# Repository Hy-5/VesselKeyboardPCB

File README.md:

# VesselKeyboardPCB
 Building a 75%(ish) custom ISO keyboard PCB

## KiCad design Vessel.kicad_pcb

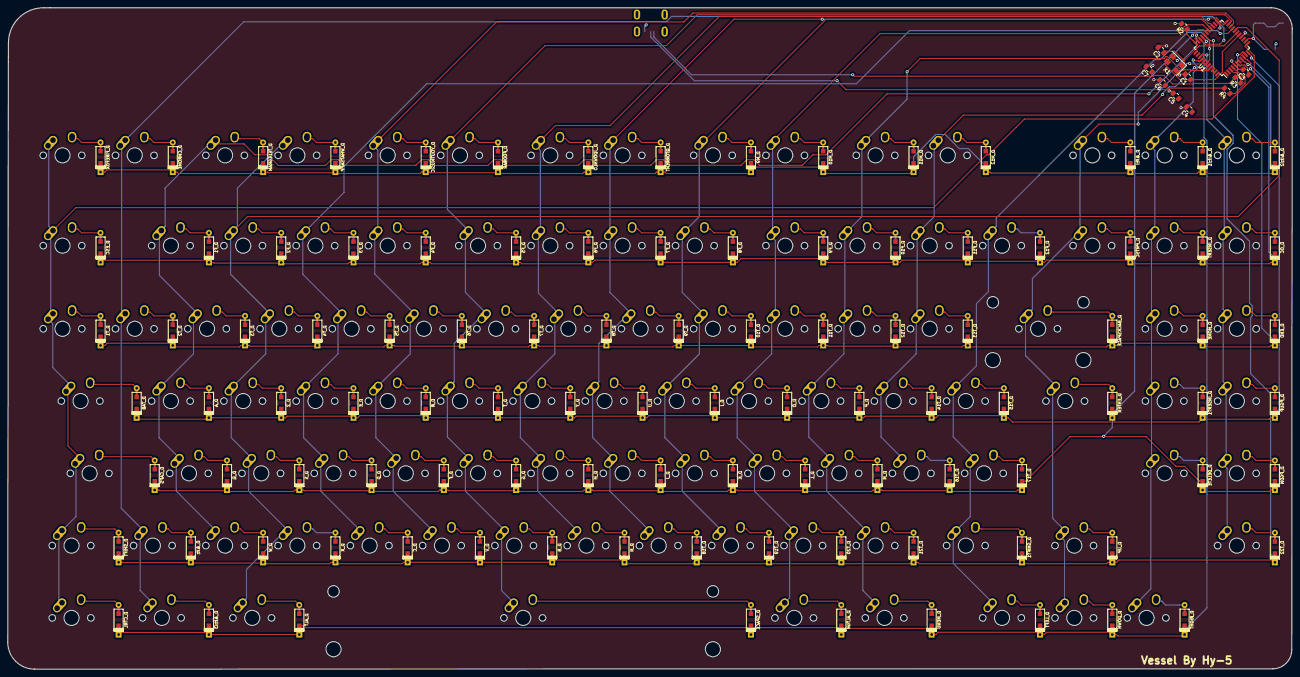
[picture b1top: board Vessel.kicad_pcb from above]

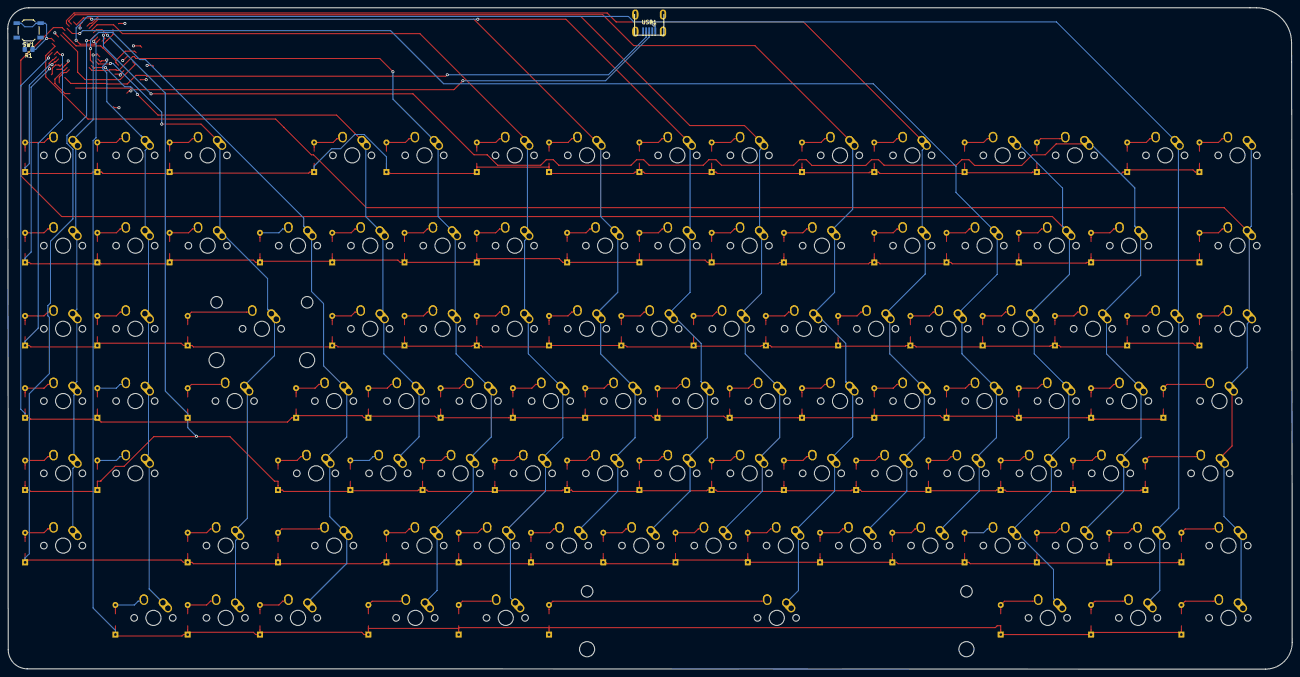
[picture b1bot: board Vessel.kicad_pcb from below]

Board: 2 copper layers, 338.6 x 174.3 mm, 219 parts (3 on the bottom side), 137 nets.

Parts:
C1, C2, C3, C4, C5, C6, C7: 22pF; C_0805_2012Metric_Pad1.15x1.40mm_HandSolder
D_&lt;: D; D_SOD123_axial
D_&lt;I, D_&lt;I1, D_&lt;I2, D_&lt;I3: D; D_SOD123_axial
D_A: D; D_SOD123_axial
D_ALT: D; D_SOD123_axial
D_ALTGR: D; D_SOD123_axial
D_B: D; D_SOD123_axial
D_BACKSPACE: D; D_SOD123_axial
D_C: D; D_SOD123_axial
D_CAPS: D; D_SOD123_axial
D_CHROME: D; D_SOD123_axial
D_CTRL: D; D_SOD123_axial
D_D: D; D_SOD123_axial
D_DELETE: D; D_SOD123_axial
D_DOWN: D; D_SOD123_axial
D_E: D; D_SOD123_axial
D_END: D; D_SOD123_axial
D_ENTER: D; D_SOD123_axial
D_ESC: D; D_SOD123_axial
D_F, D_F1, D_F2, D_F3, D_F4, D_F5, D_F6, D_F7, D_F8, D_F9, D_F10, D_F11, D_F12: D; D_SOD123_axial
D_FIREFOX: D; D_SOD123_axial
D_FOOBAR: D; D_SOD123_axial
D_G: D; D_SOD123_axial
D_H: D; D_SOD123_axial
D_HOME: D; D_SOD123_axial
D_I: D; D_SOD123_axial
D_INSERT, D_INSERT1: D; D_SOD123_axial
D_J: D; D_SOD123_axial
D_JDOWNLO: D; D_SOD123_axial
D_K: D; D_SOD123_axial
D_L: D; D_SOD123_axial
D_LEFT: D; D_SOD123_axial
D_M, D_M9, D_M10, D_M11, D_M12: D; D_SOD123_axial
D_MENU: D; D_SOD123_axial
D_N: D; D_SOD123_axial
D_O: D; D_SOD123_axial
D_OC: D; D_SOD123_axial
D_P: D; D_SOD123_axial
D_PGDN: D; D_SOD123_axial
D_PGUP: D; D_SOD123_axial
D_PRTSC: D; D_SOD123_axial
D_Q: D; D_SOD123_axial
D_QTORRENT: D; D_SOD123_axial
D_R: D; D_SOD123_axial
D_RIGHT: D; D_SOD123_axial
D_S: D; D_SOD123_axial
D_SHIFT, D_SHIFT1: D; D_SOD123_axial
D_SPACE: D; D_SOD123_axial
D_T, D_T1, D_T2, D_T3, D_T4, D_T5, D_T6, D_T7, D_T8, D_T9, D_T10, D_T11, D_T12, D_T13, D_T14, D_T15, D_T16, D_T17, D_T18, D_T19, D_T20, D_T21, D_T22: D; D_SOD123_axial
D_TAB: D; D_SOD123_axial
D_TELEGRAM: D; D_SOD123_axial
D_U: D; D_SOD123_axial
D_UP: D; D_SOD123_axial
D_V: D; D_SOD123_axial
D_W: D; D_SOD123_axial
D_WHATSAPP: D; D_SOD123_axial
D_X: D; D_SOD123_axial
D_Y: D; D_SOD123_axial
D_YOUTMUSIC: D; D_SOD123_axial
D_Z: D; D_SOD123_axial
K_&lt;: KEYSW; MX-1U-NoLED
K_&lt;I, K_&lt;I1, K_&lt;I2: KEYSW; MX-1U-NoLED
K_&lt;I3: KEYSW; MX-1.25U-NoLED
K_A: KEYSW; MX-1U-NoLED
K_ALT: KEYSW; MX-1.25U-NoLED
K_ALTGR: KEYSW; MX-1.25U-NoLED
K_B: KEYSW; MX-1U-NoLED
K_BACKSPACE: KEYSW; MX-2U-NoLED
K_C: KEYSW; MX-1U-NoLED
K_CAPS: KEYSW; MX-1.75U-NoLED
K_CHROME: KEYSW; MX-1U-NoLED
K_CTRL: KEYSW; MX-1.25U-NoLED
K_D: KEYSW; MX-1U-NoLED
K_DELETE: KEYSW; MX-1U-NoLED
K_DOWN: KEYSW; MX-1U-NoLED
K_E: KEYSW; MX-1U-NoLED
K_END: KEYSW; MX-1U-NoLED
K_ENTER: KEYSW; MX-1.25U-NoLED
K_ESC: KEYSW; MX-1U-NoLED
K_F, K_F1, K_F2, K_F3, K_F4, K_F5, K_F6, K_F7, K_F8, K_F9, K_F10, K_F11, K_F12: KEYSW; MX-1U-NoLED
K_FIREFOX: KEYSW; MX-1U-NoLED
K_FOOBAR: KEYSW; MX-1U-NoLED
K_G: KEYSW; MX-1U-NoLED
K_H: KEYSW; MX-1U-NoLED
K_HOME: KEYSW; MX-1U-NoLED
K_I: KEYSW; MX-1U-NoLED
K_INSERT, K_INSERT1: KEYSW; MX-1U-NoLED
K_J: KEYSW; MX-1U-NoLED
K_JDOWNLO: KEYSW; MX-1U-NoLED
K_K: KEYSW; MX-1U-NoLED
K_L: KEYSW; MX-1U-NoLED
K_LEFT: KEYSW; MX-1U-NoLED
K_M, K_M9, K_M10, K_M11, K_M12: KEYSW; MX-1U-NoLED
K_MENU: KEYSW; MX-1.25U-NoLED
K_N: KEYSW; MX-1U-NoLED
K_O: KEYSW; MX-1U-NoLED
K_OC: KEYSW; MX-1U-NoLED
K_P: KEYSW; MX-1U-NoLED
K_PGDN: KEYSW; MX-1U-NoLED
K_PGUP: KEYSW; MX-1U-NoLED
K_PRTSC: KEYSW; MX-1U-NoLED
K_Q: KEYSW; MX-1U-NoLED
K_QTORRENT: KEYSW; MX-1U-NoLED
K_R: KEYSW; MX-1U-NoLED
K_RIGHT: KEYSW; MX-1U-NoLED
K_S: KEYSW; MX-1U-NoLED
K_SHIFT: KEYSW; MX-1.25U-NoLED
K_SHIFT1: KEYSW; MX-1.5U-NoLED
K_SPACE: KEYSW; MX-6.25U-NoLED
K_T, K_T1, K_T2, K_T3, K_T4, K_T5, K_T6, K_T7, K_T8, K_T9, K_T10, K_T11, K_T12, K_T13, K_T14, K_T15, K_T16, K_T17, K_T18, K_T19, K_T20, K_T21, K_T22: KEYSW; MX-1U-NoLED
K_TAB: KEYSW; MX-1.5U-NoLED
K_TELEGRAM: KEYSW; MX-1U-NoLED
K_U: KEYSW; MX-1U-NoLED
K_UP: KEYSW; MX-1U-NoLED
K_V: KEYSW; MX-1U-NoLED
K_W: KEYSW; MX-1U-NoLED
K_WHATSAPP: KEYSW; MX-1U-NoLED
K_X: KEYSW; MX-1U-NoLED
K_Y: KEYSW; MX-1U-NoLED
K_YOUTMUSIC: KEYSW; MX-1U-NoLED
K_Z: KEYSW; MX-1U-NoLED
R1, R2: 10k; R_0805_2012Metric_Pad1.15x1.40mm_HandSolder
R3, R4: 22; R_0805_2012Metric_Pad1.15x1.40mm_HandSolder
SW1: SW_PUSH; SW_SPST_TL3342
U1: ATMEGA32U4; TQFP-44_10x10mm_P0.8mm
USB1: Molex-0548190589; Molex-0548190589-Assembly
X1: XTAL_GND; Crystal_SMD_5032-4Pin_5.0x3.2mm

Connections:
/col0: K_CAPS.1, K_CTRL.1, K_ESC.1, K_FIREFOX.1, K_SHIFT.1, K_T1.1, K_TAB.1, U1.12
/col1: K_&lt;.1, K_&lt;I3.1, K_CHROME.1, K_T2.1, U1.31
/col2: K_A.1, K_F1.1, K_Q.1, K_T3.1, K_TELEGRAM.1, K_W.1, U1.32
/col3: K_ALT.1, K_F2.1, K_S.1, K_T4.1, K_WHATSAPP.1, K_X.1, K_Z.1, U1.18
/col4: K_C.1, K_D.1, K_E.1, K_F3.1, K_T5.1, U1.19
/col5: K_F.1, K_F4.1, K_R.1, K_T6.1, K_V.1, K_YOUTMUSIC.1, U1.20
/col6: K_B.1, K_F5.1, K_FOOBAR.1, K_G.1, K_SPACE.1, K_T.1, K_T7.1, U1.21
/col7: K_F6.1, K_H.1, K_JDOWNLO.1, K_N.1, K_T8.1, K_Y.1, U1.25
/col8: K_F7.1, K_J.1, K_QTORRENT.1, K_T9.1, K_T18.1, K_U.1, U1.22
/col9: K_F8.1, K_I.1, K_K.1, K_M9.1, K_T10.1, K_T19.1, U1.26
/col10: K_ALTGR.1, K_F9.1, K_L.1, K_M10.1, K_O.1, K_T11.1, K_T20.1, U1.27
/col11: K_F10.1, K_M.1, K_M11.1, K_MENU.1, K_P.1, K_T12.1, K_T21.1, U1.41
/col12: K_F11.1, K_M12.1, K_T13.1, K_T14.1, K_T16.1, U1.40
/col13: K_F12.1, K_LEFT.1, K_SHIFT1.1, K_T15.1, K_T17.1, U1.39
/col14: K_&lt;I.1, K_BACKSPACE.1, K_DOWN.1, K_ENTER.1, K_PRTSC.1, K_UP.1, U1.38
/col15: K_&lt;I1.1, K_DELETE.1, K_HOME.1, K_INSERT.1, K_INSERT1.1, K_RIGHT.1, U1.37
/col16: K_&lt;I2.1, K_END.1, K_OC.1, K_PGDN.1, K_PGUP.1, K_T22.1, U1.36
/row0: D_&lt;I.1, D_&lt;I1.1, D_&lt;I2.1, D_CHROME.1, D_FIREFOX.1, D_FOOBAR.1, D_JDOWNLO.1, D_M9.1, D_M10.1, D_M11.1, D_M12.1, D_QTORRENT.1, D_TELEGRAM.1, D_WHATSAPP.1, D_YOUTMUSIC.1, U1.8
/row1: D_ESC.1, D_F1.1, D_F2.1, D_F3.1, D_F4.1, D_F5.1, D_F6.1, D_F7.1, D_F8.1, D_F9.1, D_F10.1, D_F11.1, D_F12.1, D_INSERT.1, D_OC.1, D_PRTSC.1, U1.9
/row2: D_BACKSPACE.1, D_END.1, D_HOME.1, D_T1.1, D_T2.1, D_T3.1, D_T4.1, D_T5.1, D_T6.1, D_T7.1, D_T8.1, D_T9.1, D_T10.1, D_T11.1, D_T12.1, D_T13.1, U1.10
/row3: D_A.1, D_E.1, D_I.1, D_INSERT1.1, D_O.1, D_P.1, D_PGUP.1, D_R.1, D_T.1, D_T14.1, D_T15.1, D_TAB.1, D_U.1, D_Y.1, D_Z.1, U1.11
/row4: D_CAPS.1, D_D.1, D_DELETE.1, D_ENTER.1, D_F.1, D_G.1, D_H.1, D_J.1, D_K.1, D_L.1, D_M.1, D_PGDN.1, D_Q.1, D_S.1, D_T16.1, D_T17.1, U1.28
/row5: D_&lt;.1, D_B.1, D_C.1, D_N.1, D_SHIFT.1, D_SHIFT1.1, D_T18.1, D_T19.1, D_T20.1, D_T21.1, D_T22.1, D_UP.1, D_V.1, D_W.1, D_X.1, U1.29
/row6: D_&lt;I3.1, D_ALT.1, D_ALTGR.1, D_CTRL.1, D_DOWN.1, D_LEFT.1, D_MENU.1, D_RIGHT.1, D_SPACE.1, U1.30
GND: C1.2, C2.2, C3.2, C4.2, C5.2, C6.2, C7.2, R2.2, SW1.1, U1.5, U1.15, U1.23, USB1.1, X1.2, X1.4
unnamed: C1.1, U1.16, X1.1
unnamed: C2.1, U1.17, X1.3
unnamed: C3.1, U1.6
unnamed: D_&lt;.2, K_&lt;.2
unnamed: D_&lt;I1.2, K_&lt;I1.2
unnamed: D_&lt;I2.2, K_&lt;I2.2
unnamed: D_&lt;I3.2, K_&lt;I3.2
unnamed: D_&lt;I.2, K_&lt;I.2
unnamed: D_A.2, K_A.2
unnamed: D_ALT.2, K_ALT.2
unnamed: D_ALTGR.2, K_ALTGR.2
unnamed: D_B.2, K_B.2
unnamed: D_BACKSPACE.2, K_BACKSPACE.2
unnamed: D_C.2, K_C.2
unnamed: D_CAPS.2, K_CAPS.2
unnamed: D_CHROME.2, K_CHROME.2
unnamed: D_CTRL.2, K_CTRL.2
unnamed: D_D.2, K_D.2
unnamed: D_DELETE.2, K_DELETE.2
unnamed: D_DOWN.2, K_DOWN.2
unnamed: D_E.2, K_E.2
unnamed: D_END.2, K_END.2
unnamed: D_ENTER.2, K_ENTER.2
unnamed: D_ESC.2, K_ESC.2
unnamed: D_F1.2, K_F1.2
unnamed: D_F2.2, K_F2.2
unnamed: D_F3.2, K_F3.2
unnamed: D_F4.2, K_F4.2
unnamed: D_F5.2, K_F5.2
unnamed: D_F6.2, K_F6.2
unnamed: D_F7.2, K_F7.2
unnamed: D_F8.2, K_F8.2
unnamed: D_F9.2, K_F9.2
unnamed: D_F10.2, K_F10.2
unnamed: D_F11.2, K_F11.2
unnamed: D_F12.2, K_F12.2
unnamed: D_F.2, K_F.2
unnamed: D_FIREFOX.2, K_FIREFOX.2
unnamed: D_FOOBAR.2, K_FOOBAR.2
unnamed: D_G.2, K_G.2
unnamed: D_H.2, K_H.2
unnamed: D_HOME.2, K_HOME.2
unnamed: D_I.2, K_I.2
unnamed: D_INSERT1.2, K_INSERT1.2
unnamed: D_INSERT.2, K_INSERT.2
unnamed: D_J.2, K_J.2
unnamed: D_JDOWNLO.2, K_JDOWNLO.2
unnamed: D_K.2, K_K.2
unnamed: D_L.2, K_L.2
unnamed: D_LEFT.2, K_LEFT.2
unnamed: D_M9.2, K_M9.2
unnamed: D_M10.2, K_M10.2
unnamed: D_M11.2, K_M11.2
unnamed: D_M12.2, K_M12.2
unnamed: D_M.2, K_M.2
unnamed: D_MENU.2, K_MENU.2
unnamed: D_N.2, K_N.2
unnamed: D_O.2, K_O.2
unnamed: D_OC.2, K_OC.2
unnamed: D_P.2, K_P.2
unnamed: D_PGDN.2, K_PGDN.2
unnamed: D_PGUP.2, K_PGUP.2
unnamed: D_PRTSC.2, K_PRTSC.2
unnamed: D_Q.2, K_Q.2
unnamed: D_QTORRENT.2, K_QTORRENT.2
unnamed: D_R.2, K_R.2
unnamed: D_RIGHT.2, K_RIGHT.2
unnamed: D_S.2, K_S.2
unnamed: D_SHIFT1.2, K_SHIFT1.2
unnamed: D_SHIFT.2, K_SHIFT.2
unnamed: D_SPACE.2, K_SPACE.2
unnamed: D_T1.2, K_T1.2
unnamed: D_T2.2, K_T2.2
unnamed: D_T3.2, K_T3.2
unnamed: D_T4.2, K_T4.2
unnamed: D_T5.2, K_T5.2
unnamed: D_T6.2, K_T6.2
unnamed: D_T7.2, K_T7.2
unnamed: D_T8.2, K_T8.2
unnamed: D_T9.2, K_T9.2
unnamed: D_T10.2, K_T10.2
unnamed: D_T11.2, K_T11.2
unnamed: D_T12.2, K_T12.2
unnamed: D_T13.2, K_T13.2
unnamed: D_T14.2, K_T14.2
unnamed: D_T15.2, K_T15.2
unnamed: D_T16.2, K_T16.2
unnamed: D_T17.2, K_T17.2
unnamed: D_T18.2, K_T18.2
unnamed: D_T19.2, K_T19.2
unnamed: D_T20.2, K_T20.2
unnamed: D_T21.2, K_T21.2
unnamed: D_T22.2, K_T22.2
unnamed: D_T.2, K_T.2
unnamed: D_TAB.2, K_TAB.2
unnamed: D_TELEGRAM.2, K_TELEGRAM.2
unnamed: D_U.2, K_U.2
unnamed: D_UP.2, K_UP.2
unnamed: D_V.2, K_V.2
unnamed: D_W.2, K_W.2
unnamed: D_WHATSAPP.2, K_WHATSAPP.2
unnamed: D_X.2, K_X.2
unnamed: D_Y.2, K_Y.2
unnamed: D_YOUTMUSIC.2, K_YOUTMUSIC.2
unnamed: D_Z.2, K_Z.2
unnamed: R1.1, SW1.2, U1.13
unnamed: R2.1, U1.33
unnamed: R3.1, U1.3
unnamed: R4.1, U1.4
unnamed: R3.2, USB1.2
unnamed: R4.2, USB1.3
VCC: C4.1, C5.1, C6.1, C7.1, R1.2, U1.2, U1.14, U1.24, USB1.5

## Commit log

2023-10-16 Initial Commit - Build mostly finished
2023-10-16 Default layout name modified
2023-10-17 Routing Done - Via lowered
2023-10-18 Final routing done
